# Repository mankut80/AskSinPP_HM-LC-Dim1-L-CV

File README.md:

# HM-LC-DIM1L-CV

## 230V Dimmeraktor (Phasenanschnitt)

*Hinweis zum Bild: das Netzteil HLK-PM01 im Bild ist in Wahrheit ein HLK-PM03 mit 3.3V Ausgangsspannung. Ich hatte leider kein passendes 3D-Modell gefunden.*

### Funktion

Mit der Technik des Phasenanschnitts lassen sich ohmsche und induktive Wechselstromlasten in der Leistung steuern. Da heutzutage wohl kaum noch jemand ein Interesse daran hat, Glühlampen zu dimmen, wird diese Schaltung eher für Motoren oder Transformatoren eingesetzt werden (Ventilatoren, Abluftmotoren). Über zwei Schraubklemmleisten wird sowohl die Netzspannung als auch der Verbraucher angeschlossen.

### Schaltungsbeschreibung

Siehe [PDF](pcb/HM-LC-DIM1L-CV_Schaltplan.pdf?fileId=26955)

Die benötigte Spannung von 3.3V wird vom PCB-Netzteil PS1 bereitgestellt und dient zur Versorgung des Arduino und des CC1101-Funkmoduls.

Ein diskret aufgebauter Nullspannungsdetektor liefert im Nulldurchgang der Netzspannung einen kurzen Impuls, welcher über den Optokoppler U1 an den Microcontroller gemeldet wird.

Der Leistungsteil besteht aus einem Optokoppler mit TRIAC-Ausgang welcher vom Arduino angesteuert wird, dem Leistungs-TRIAC und ein paar Filterbauteilen um Strom-/Spannungsspitzen zu dämpfen.  
Die Programmierung geschieht entweder wie üblich über den FTDI-Adapter direkt am Arduino oder über die ISP-Schnittstelle, herausgeführt an J1. J1 ist zugegeben nicht ganz die feine Art. Es ist ein in der Arduinowelt eher unüblicher Steckverbinder von Molex (Picoblade), den ich für private Zwecke gerne nutze. Er kann aber auch einfach weggelassen werden. Wer keine OTA-Updates braucht und somit nicht auf die Programmierung per ISP angewiesen ist, wird das nicht vermissen.

### Hinweise

Q1 und Q2, die beiden bipolaren Transistoren im Nulldurchgangsdetektor, können durch andere Standardtransistoren ersetzt werden. Sie müssen keine besonderen Merkmale aufweisen.  
Das Netzteil PS1 ist hoffnungslos überdimensionert, da würde auch eine Variante mit 200mA Ausgangstrom dicke ausreichen. Allerdings gab es diese Dinger nicht in einer kleineren Variante und auf ein Kondensator-"Netzteil" hatte ich keine Lust, da wäre das flashen mangels galvanischer Trennung zum Abenteuer geworden.

Der Haupt-TRIAC D6 kann auch durch andere Typen ersetzt werden. Die Wahl fiel von meiner Seite aus auf den BT138 weil mir dieser in Massen zur Verfügung steht ;-). Wer besonders kleine Leistungen schalten will, mag eventuell einen TRIAC mit kleinerem Haltestrom bevorzugen. Beim BT138 liegt dieser Haltestrom zwischen 4 und 30mA. In der Praxis bedeutet ein zu großer Haltestrom, dass die Last bei niedriger Leistungseinstellung zu flackern beginnt und eine ordentliche Steuerung erst ab höheren Steuergraden (>50%) möglich ist.

Der Heißleiter TH1 ist ebenfalls optional. Er dient zur Überwachung der Gehäuseinnentemperatur. Bei Bedarf kann man die Anschlüsse verlängern und ihn in der Nähe des Kühlkörpers platzieren. Oder ihn ganz weglassen (und im .ino-File auskommentieren).

#### Achtung 230V!

Bitte Vorsicht beim Nachbau. Wird der TRIAC ohne Isolierung am Kühlkörper angebracht, steht dieser unter Spannung, da fasst man leicht mal hin. Beim Anschluss des Verbrauchers darauf achten, dass dieser die Phase eventuell an einem bestimmten Anschluss haben will (z.B. bei einer Lampenfassung, da darf das Gewinde nicht auf die Phase gelegt werden). Rein von der Funktion her ist es egal, wo Phase und wo N angeschlossen wird.

### Bauteilliste

| Pos | Ref | Wert |
|-----|-----|------|
| 1 | C3, C4 | 47nF / 400V , RM 7.5, 10.3x7.5mm |
| 2 | C1, C2 | 100nF / 400V , RM 7.5, 10.3x7.5mm |
| 3 | R1, R2 | 470k, Bauform 0207, 1/4W |
| 4 | R3 | 330R, Bauform 0207, 1/4W |
| 5 | R4 | 150R, Bauform 0207, 1/4W |
| 6 | R5 | 360R, Baeeuform 0207, 1/4W |
| 7 | R6, R7 | 470R, Bauform 0207, 1/4W |
| 8 | R8 | 10k, Bauform 0207, 1/4W |
| 9 | R9 | 10k, Bauform 0207, 1/4W |
| 10 | L1, L2 | 100µH, 6A, Spule, z.B. Würth WUE 7447070 (bei Reichelt) |
| 11 | D1 - D4 | 1N4007 Gleichrichterdiode |
| 12 | D5 | LED, 3mm, Farbe egal |
| 13 | D6 | TRIAC BT138-600, TO220-Gehäuse |
| 14 | U1 | LTV-817 Optokoppler, DIP4 |
| 15 | U2 | MOC3052M Optokoppler mit TRIAC-Ausgang, DIP6 |
| 16 | U3 | CC1101-Funkmodul |
| 17 | X1, X2 | Schraubklemme 2pol., RM 5.08 oder RM5.00 |
| 18 | F1 | Sicherungshalter für Feinsicherungen 5x20mm und Sicherung 4A mittelträge |
| 19 | SW1 | Kurzhubtaster 6x6mm |
| 20 | A1 | Arduino Pro Mini 3.3V, 8MHz |
| 21 | PS1 | HLK-PM03 von HiLink, Netzteil 3.3V |
| 22 | Q1 | BC547, TO92, NPN-Transistor |
| 23 | Q2 | BC557, TO92, PNP-Transistor |
| 24 | TH1 | NTC 10k, Heißleiter, RM 2.5 |
| 25 | HS1 | Kühlkörper SK104 von Fischer |
| 26 | J1 | Molex Picoblade 53047-0610, Steckverbinder für ISP |

### Gehäuse

Das Gehäuse wurde in FreeCAD entworfen, die [Originaldatei](CAD/HM_AsksinPP_Phasenanschnitt_Gehaeuse.FCStd?fileId=26970) und zwei Step-Dateien ([Deckel](CAD/HM_AsksinPP_Phasenanschnitt_Gehaeuse-Oberteil.step?fileId=26968) und [Boden](CAD/HM_AsksinPP_Phasenanschnitt_Gehaeuse-Unterteil.step?fileId=26969)) zum Import in den Slicer (Prusaslicer frisst direkt step-Dateien) sind im CAD-Verzeichnis zu finden. Die lustigen, gezackten Vertiefungen für die Anschlussleitungen dienen als Zugentlastung. Im Deckel sind zwei kleine rechteckige Vertiefungen für Beschriftungsbänder, so man denn will.

Fertig aufgebaut sieht es dann so aus:

Das Bild zeigt noch die Platine in der Revision A (aktuell ist C) mit einigen Fehlern, deshalb gleicht sie nicht 100%ig dem Bestückungsplan. Das CC1101-Modul hat als Antenne eine 83mm lange Litzenleitung bekommen, die sich im Gehäuse in einem kleinen Schlitz an der Seite verlegen lässt.

### Sketch

Als Sketch kommt eine abgeänderte Vorlage aus dem Asksin-Repo zum EInsatz. Die Serial muss natürlich geändert werden, außerdem ...

Ohne die  folgenden Änderungen wird nach dem EInschalten wiederholt (alle 40ms) kurz eingeschaltet, außerdem schaltet er nicht zuverlässig aus (geht manchmal auf Dauer-AN)

im main (\*.ino)-file, Funktion void setup():

```
phaseCut.stop();
```

innerhalb void loop():

```
if(!phaseCut.isrunning()) digitalWrite(DIMMERPIN, false);
```

Ohne die  folgenden Änderungen wird bei einer Dim-Einstellung von "0" auf Dauer-An gestellt:  
PhaseCut.cpp, Zeile 130:

```
if (_timer < 76 ) digitalWrite(OUTPUT_PIN, HIGH);
```
PhaseCut.cpp, Zeile 113, korrigieren des Setzens der Bits von Register TCCR2B (ist eher kosmetischer Natur):
```
TCCR2B |= (1 << CS20) | (1 << CS21) | (1 << CS22) ;
```

PWM.h, Zeile 25:

```
static const uint8_t zctable[50] PROGMEM = {
 9, 12, 13, 14, 15, 16, 17, 18, 19, 20, 21, 22, 23, 24, 25,26, 27, 28, 29, 30, 31, 32, 33, 34, 35, 36, 37, 38, 39, 40,41, 42, 43, 44, 45, 46, 47, 48, 49, 50, 53, 55, 60, 62, 64, 68, 70, 72, 76
};
```

PWM.h, Zeile 86:

```
#if PHASECUTMODE == 1    
  uint8_t offset = (STEPS - value)*49/STEPS;
```

Außerdem noch diese Änderung:
PhaseCut.h, Zeilen 10-16: 
Die Definitionen für PHASECUTMODE und ZEROPIN müssen abgeändert werden. Diese werden seltsamerweise nicht aus dem *.ino-File übernommen (vielen Dank an ivo-int für die Nachreichung dieser Information):

```
#ifndef PHASECUTMODE
#define PHASECUTMODE 1
#endif 

#ifndef ZEROPIN
#define ZEROPIN 3
#endif
```

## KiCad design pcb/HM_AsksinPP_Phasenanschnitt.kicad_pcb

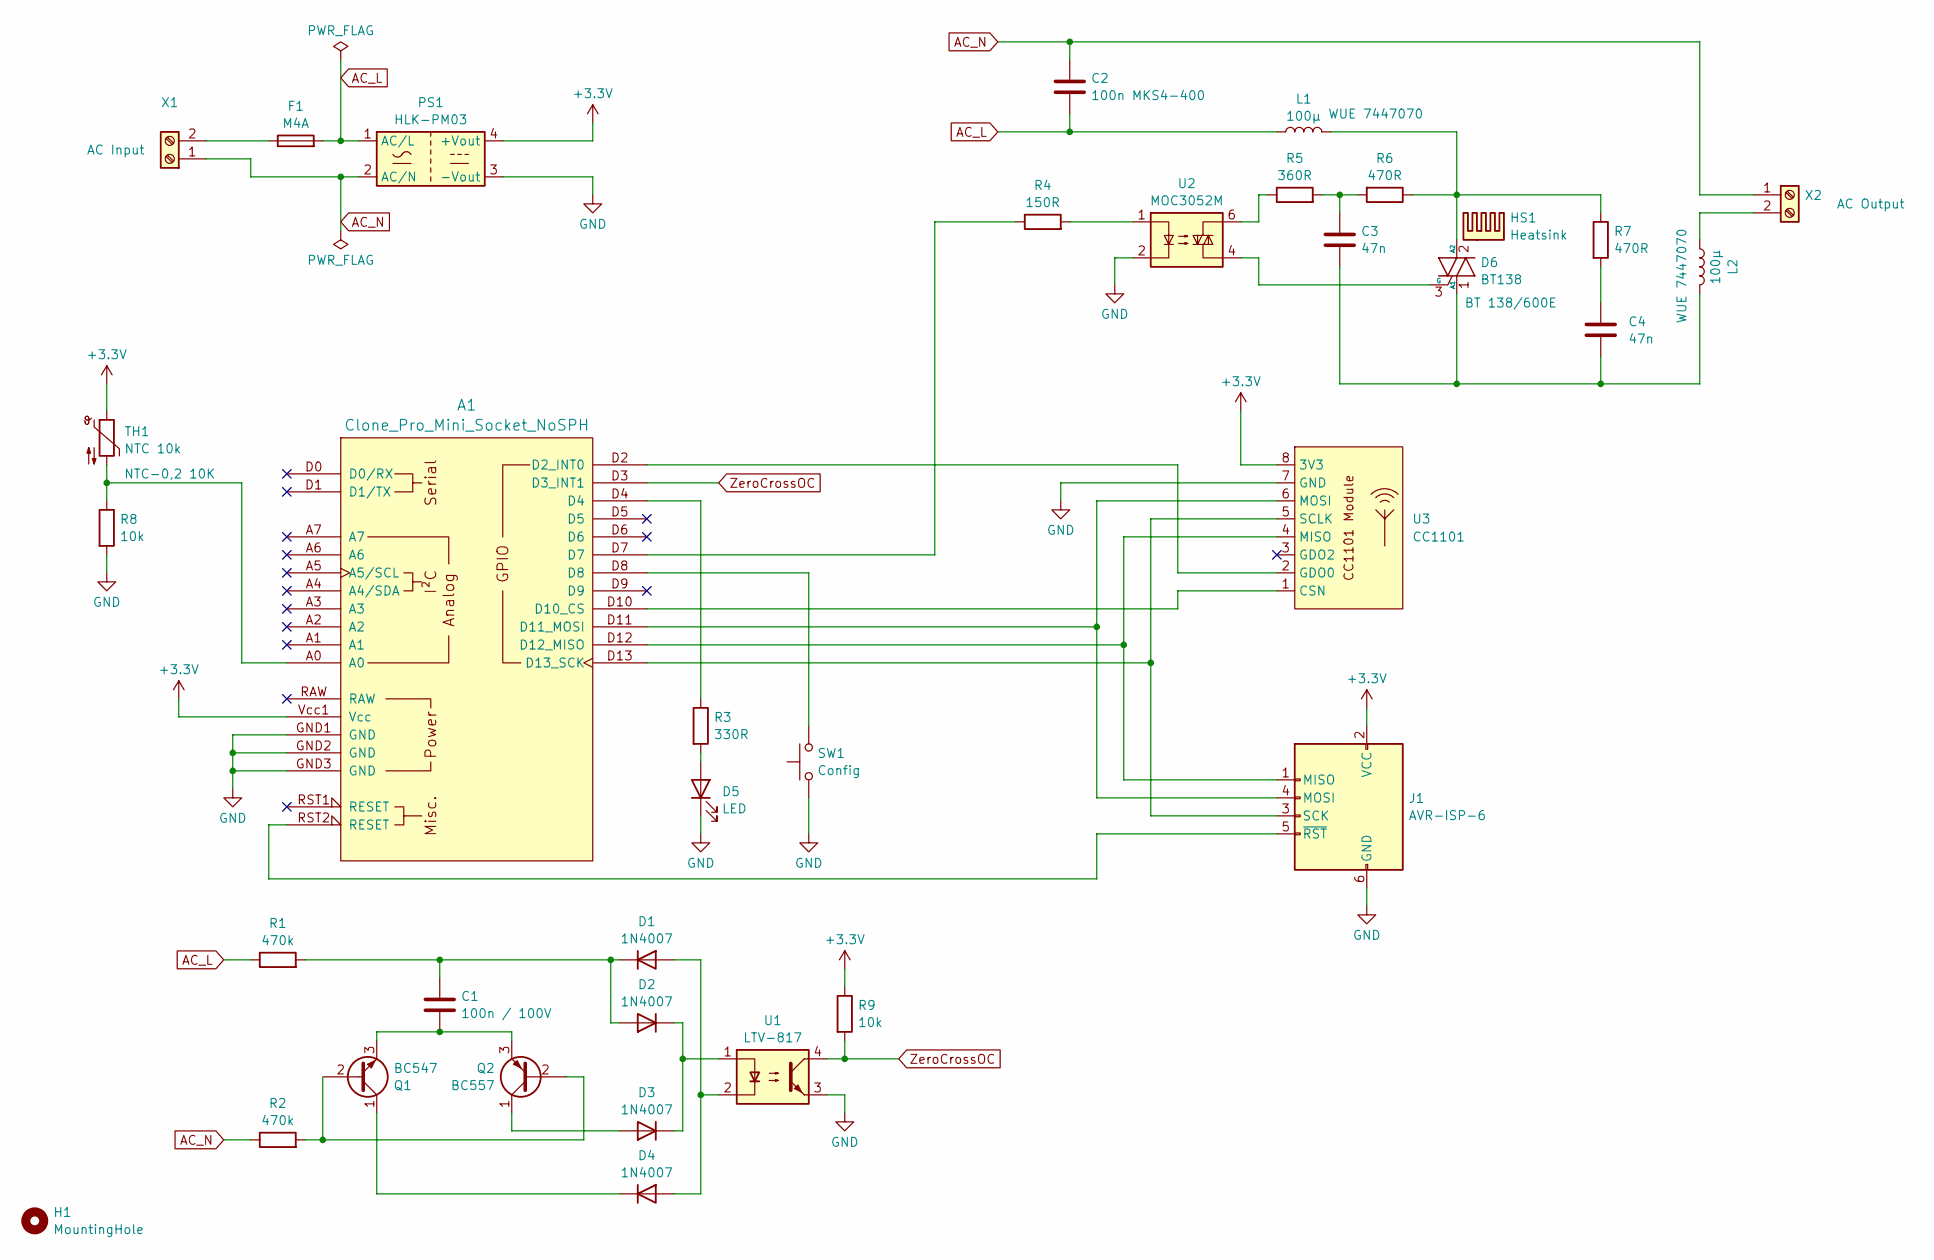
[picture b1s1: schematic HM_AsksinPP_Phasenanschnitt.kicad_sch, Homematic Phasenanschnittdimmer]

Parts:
A1: Clone_Pro_Mini_Socket_NoSPH
C1: 100n / 100V; C_Rect_L10.3mm_W5.0mm_P7.50mm_MKS4
C2: 100n MKS4-400; C_Rect_L10.3mm_W5.0mm_P7.50mm_MKS4
C3, C4: 47n; C_Rect_L10.3mm_W5.7mm_P7.50mm_MKS4
D1, D2, D3, D4: 1N4007; D_DO-41_SOD81_P10.16mm_Horizontal
D5: LED; LED_D3.0mm
D6: BT138; TO-220-3_Vertical
F1: M4A; Fuseholder_Cylinder-5x20mm_Stelvio-Kontek_PTF78_Horizontal_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
H1: MountingHole; MountingHole_3.2mm_M3
HS1: Heatsink; Heatsink_Fischer_SK104-STCB_35x13mm__2xDrill3.5mm_ScrewM3
J1: AVR-ISP-6; Molex_PicoBlade_53047-0610_1x06_P1.25mm_Vertical
L1, L2: 100µ; L_Toroid_Vertical_L22.4mm_W10.2mm_P7.90mm_Vishay_TJ4
PS1: HLK-PM03; Converter_ACDC_HiLink_HLK-PMxx
Q1: BC547; TO-92_Inline
Q2: BC557; TO-92_Inline
R1, R2: 470k; R_Axial_DIN0207_L6.3mm_D2.5mm_P2.54mm_Vertical
R3: 330R; R_Axial_DIN0207_L6.3mm_D2.5mm_P7.62mm_Horizontal
R4: 150R; R_Axial_DIN0207_L6.3mm_D2.5mm_P2.54mm_Vertical
R5: 360R; R_Axial_DIN0207_L6.3mm_D2.5mm_P2.54mm_Vertical
R6, R7: 470R; R_Axial_DIN0207_L6.3mm_D2.5mm_P2.54mm_Vertical
R8: 10k; R_Axial_DIN0207_L6.3mm_D2.5mm_P7.62mm_Horizontal
R9: 10k; R_Axial_DIN0207_L6.3mm_D2.5mm_P2.54mm_Vertical
SW1: Config; SW_PUSH_6mm_H5mm
TH1: NTC 10k; C_Disc_D3.8mm_W2.6mm_P2.50mm
U1: LTV-817; DIP-4_W7.62mm
U2: MOC3052M; DIP-6_W7.62mm_LongPads
U3: CC1101; CC1101_Module_v1
X1, X2: Screw_Terminal_01x02; TerminalBlock_Altech_AK300-2_P5.00mm

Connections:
+3.3V: A1.Vcc1 (Vcc), J1.2 (VCC), PS1.4 (+Vout), R9.1, TH1.1, U3.8 (3V3)
AC_L: C2.2, F1.2, L1.1, PS1.1 (AC/L), R1.1
AC_N: C2.1, PS1.2 (AC/N), R2.1, X1.1, X2.1
GND: A1.GND1 (GND), A1.GND2 (GND), A1.GND3 (GND), D5.1 (K), J1.6 (GND), PS1.3 (-Vout), R8.2, SW1.1, U1.3, U2.2, U3.7 (GND)
unnamed: A1.D2 (D2_INT0), U3.2 (GDO0)
unnamed: A1.D10 (D10_CS), U3.1 (CSN)
unnamed: A1.D11 (D11_MOSI), J1.4 (MOSI), U3.6 (MOSI)
unnamed: A1.D12 (D12_MISO), J1.1 (MISO), U3.4 (MISO)
unnamed: A1.D13 (D13_SCK), J1.3 (SCK), U3.5 (SCLK)
unnamed: A1.A0, R8.1, TH1.2
unnamed: A1.D4, R3.1
unnamed: A1.D7, R4.1
unnamed: A1.D8, SW1.2
unnamed: C3.1, R5.2, R6.2
unnamed: C4.1, R7.2
unnamed: D1.2 (A), D4.2 (A), U1.2
unnamed: C1.1, D1.1 (K), D2.2 (A), R1.2
unnamed: D2.1 (K), D3.1 (K), U1.1
unnamed: D3.2 (A), Q2.1 (C)
unnamed: D4.1 (K), Q1.1 (C)
unnamed: D5.2 (A), R3.2
unnamed: D6.2 (A2), L1.2, R6.1, R7.1
unnamed: C3.2, C4.2, D6.1 (A1), L2.2
unnamed: D6.3 (G), U2.4
unnamed: A1.RST2 (RESET), J1.5 (~RST)
unnamed: Q1.2 (B), Q2.2 (B), R2.2
unnamed: C1.2, Q1.3 (E), Q2.3 (E)
unnamed: R4.2, U2.1
unnamed: R5.1, U2.6
unnamed: F1.1, X1.2
unnamed: L2.1, X2.2
ZeroCrossOC: A1.D3 (D3_INT1), R9.2, U1.4

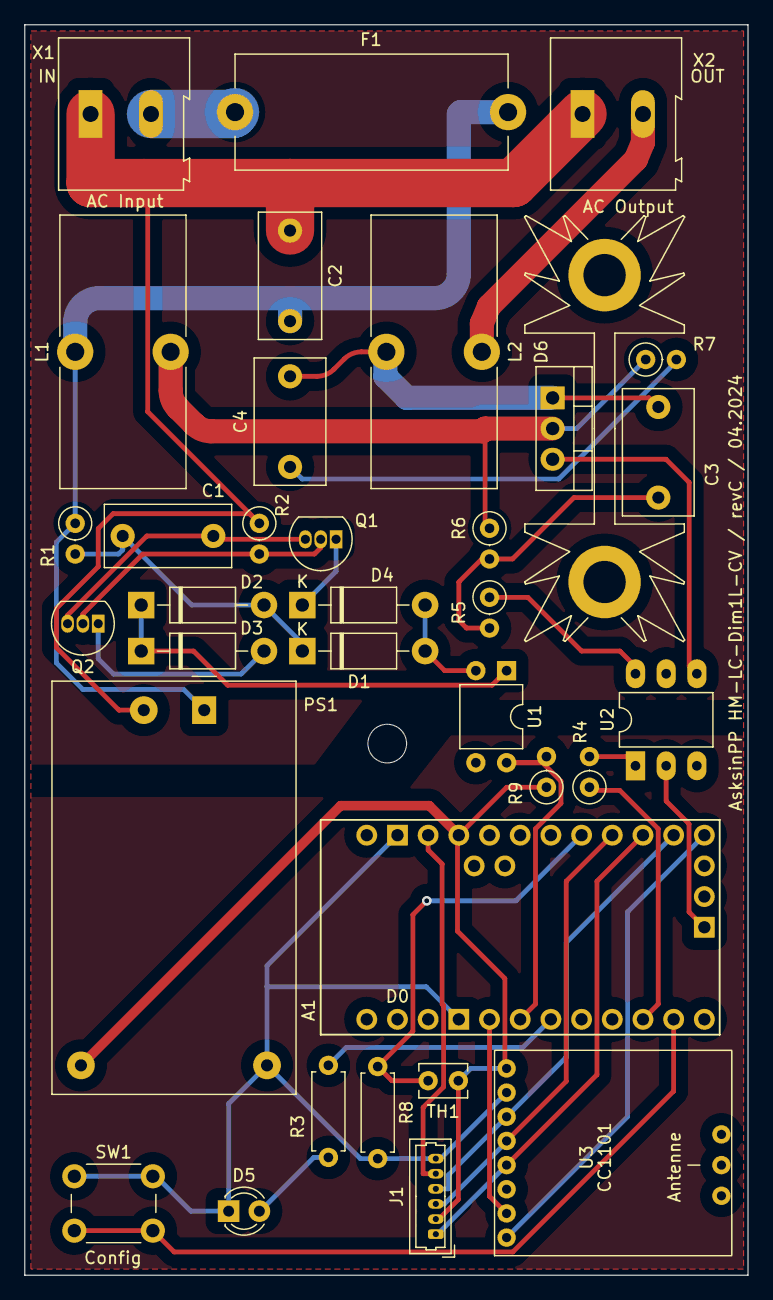
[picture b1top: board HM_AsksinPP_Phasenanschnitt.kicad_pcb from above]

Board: 2 copper layers, 59.9 x 103.5 mm, 36 parts (0 on the bottom side), 32 nets.

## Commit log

2024-04-09 changed ProjectURL
2024-10-25 Update HM-LC-DIM1L-CV.ino
    deleted '#include <Arduino>', which is only neccessary for platformIO-Users
2024-10-25 Update README.md
    Hinweis zur notwendigen Änderung der PhaseCut.h hinzugefügt
2024-10-25 Update README.md
    Hinweis zur Änderung von TCCR2B in PhaseCut.cpp hinzugfügt
